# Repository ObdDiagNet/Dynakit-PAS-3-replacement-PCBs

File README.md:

Dynakit PAS-3 replacement PCBs
==========================================
A set of circuit boards for PAS-3 preamplifier including PC-5 line Stage and PC-6 Phono Stage plus Capacitor Board.

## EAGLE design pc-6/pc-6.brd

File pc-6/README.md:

Dynakit PAS-3 PC-6 Phono Stage circuit board
==========================================
The boards retain the original Dynakit PAS circuitry but uses available PCB through hole capacitors.
The boards retain the original Dynakit PAS circuitry but uses available through hole capacitors. Original solder pad numbering is retained and silk-screened on circuit board.

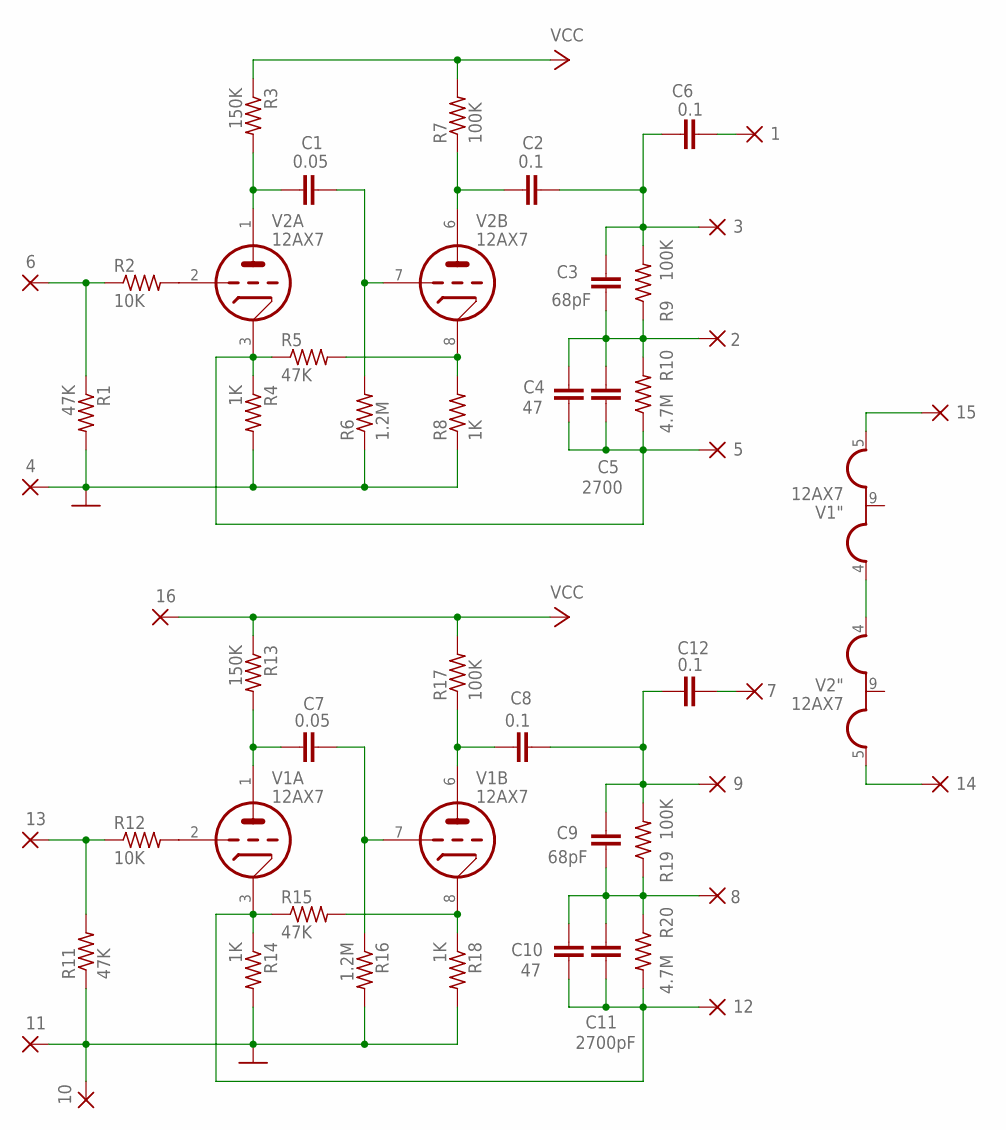
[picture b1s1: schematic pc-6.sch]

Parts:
1, 2, 3, 4, 5, 6, 7, 8, 9, 10, 11, 12, 13, 14, 15, 16: WIREPAD3,17/1,3M; 3,17/1,13M
C1, C7: 0.05; C10B4
C2, C6, C8, C12: 0.1; C10B4
C3, C9: 68pF; C5B2.5
C4, C10: 47; C5B2.5
C5: 2700; C5B2.5
C11: 2700pF; C5B2.5
R1, R5, R11, R15: 47K; 0411/15
R2, R12: 10K; 0411/15
R3, R13: 150K; 0411/15
R4, R8, R14, R18: 1K; 0411/15
R6, R16: 1.2M; 0411/15
R7, R9, R17, R19: 100K; 0411/15
R10, R20: 4.7M; 0411/15
V1, V2: 12AX7; NOVAL

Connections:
GND: 4.1, 10.1, 11.1, R1.2, R4.2, R6.1, R8.1, R11.1, R14.2, R16.2, R18.2
unnamed: C7.2, R13.2, V1.1 (TA)
unnamed: R12.2, V1.2 (TG)
unnamed: 8.1, C9.1, C10.1, C11.1, R19.1, R20.1
unnamed: 7.1, C12.2
unnamed: C7.1, R16.1, V1.7 (TG)
unnamed: C1.1, R6.2, V2.7 (TG)
unnamed: 3.1, C2.1, C3.2, C6.1, R9.2
unnamed: 13.1, R11.2, R12.1
unnamed: R15.2, R18.1, V1.8 (TK)
unnamed: C8.1, R17.1, V1.6 (TA)
unnamed: 9.1, C8.2, C9.2, C12.1, R19.2
unnamed: C1.2, R3.2, V2.1 (TA)
unnamed: R2.2, V2.2 (TG)
unnamed: 12.1, C10.2, C11.2, R14.1, R15.1, R20.2, V1.3 (TK)
unnamed: 2.1, C3.1, C4.1, C5.1, R9.1, R10.2
unnamed: 1.1, C6.2
unnamed: R5.2, R8.2, V2.8 (TK)
unnamed: C2.2, R7.1, V2.6 (TA)
unnamed: 5.1, C4.2, C5.2, R4.1, R5.1, R10.1, V2.3 (TK)
unnamed: 6.1, R1.1, R2.1
unnamed: 15.1, V1.5 (H3)
unnamed: 14.1, V2.5 (H3)
unnamed: V1.4 (H1), V2.4 (H1)
VCC: 16.1, R3.1, R7.2, R13.1, R17.2

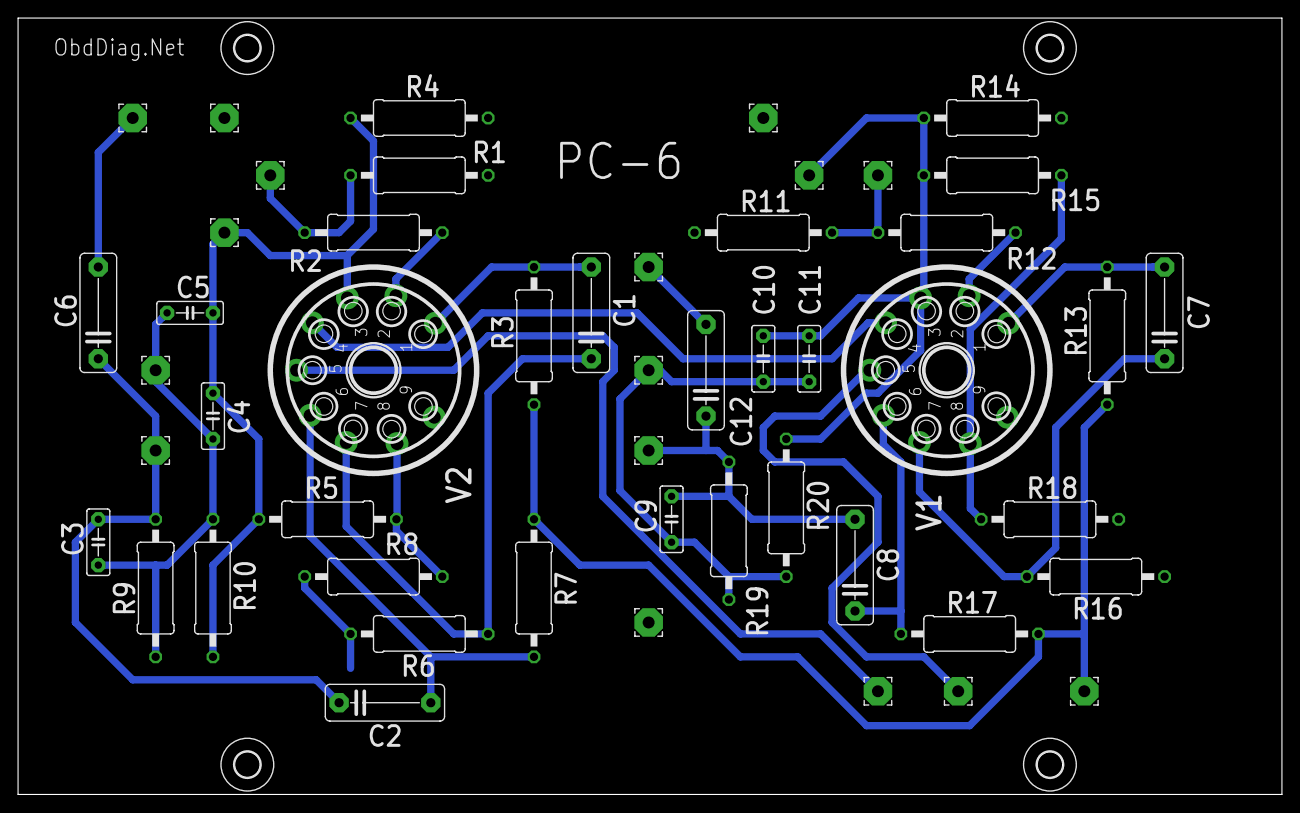
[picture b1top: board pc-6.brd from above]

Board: 2 copper layers, 140.0 x 86.0 mm, 54 parts (0 on the bottom side), 25 nets.

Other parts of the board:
U$1, U$2, U$3, U$4: 2,8

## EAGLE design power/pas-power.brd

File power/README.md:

Dynaco PAS-3 Capacitor Board
==========================================

This board replaces the large can capacitor in the power supply section of the Dynaco PAS-3 preamplifier, as well as the selenium filament rectifier and 
the two large filament filter caps. Exact replacements for the original can capacitors are difficult to find. The board uses readily available PCB through hole capacitors.

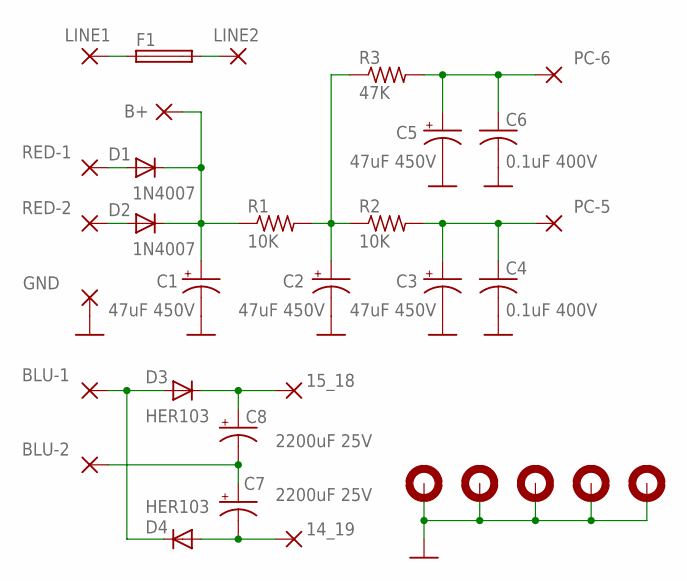
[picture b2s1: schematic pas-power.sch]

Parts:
14_19, 15_18: 3,81/1,4
B+: 3,81/1,4
BLU-1, BLU-2: 3,81/1,4
C1, C2, C3, C5: 47uF 450V; E7,5-16
C4, C6: 0.1uF 400V; C102-043X133
C7, C8: 2200uF 25V; E5-10,5
D1, D2: 1N4007; DO41-10
D3, D4: HER103; DO41-10
F1: FUSESHK20L; SHK20L
GND: 3,81/1,4
H1: MOUNT-PAD-ROUND4.3; 4,3-PAD
H2, H3, H4, H5: MOUNT-PAD-ROUND3.3; 3,3-PAD
LINE1, LINE2: 3,81/1,4
PC-5, PC-6: 3,81/1,4
R1, R2: 10K; 0309/12
R3: 47K; 0309/12
RED-1, RED-2: 3,81/1,4

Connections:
GND: C1.-, C2.-, C3.-, C4.2, C5.-, C6.2, GND.1, H1.B4,3, H2.B3,3, H3.B3,3, H4.B3,3, H5.B3,3
unnamed: D1.A, RED-1.1
unnamed: D2.A, RED-2.1
unnamed: B+.1, C1.+, D1.C, D2.C, R1.1
unnamed: C2.+, R1.2, R2.1, R3.1
unnamed: C3.+, C4.1, PC-5.1, R2.2
unnamed: BLU-1.1, D3.A, D4.C
unnamed: C5.+, C6.1, PC-6.1, R3.2
unnamed: 14_19.1, C7.-, D4.A
unnamed: 15_18.1, C8.+, D3.C
unnamed: BLU-2.1, C7.+, C8.-
unnamed: F1.2A (2), LINE2.1
unnamed: F1.1A (1), LINE1.1

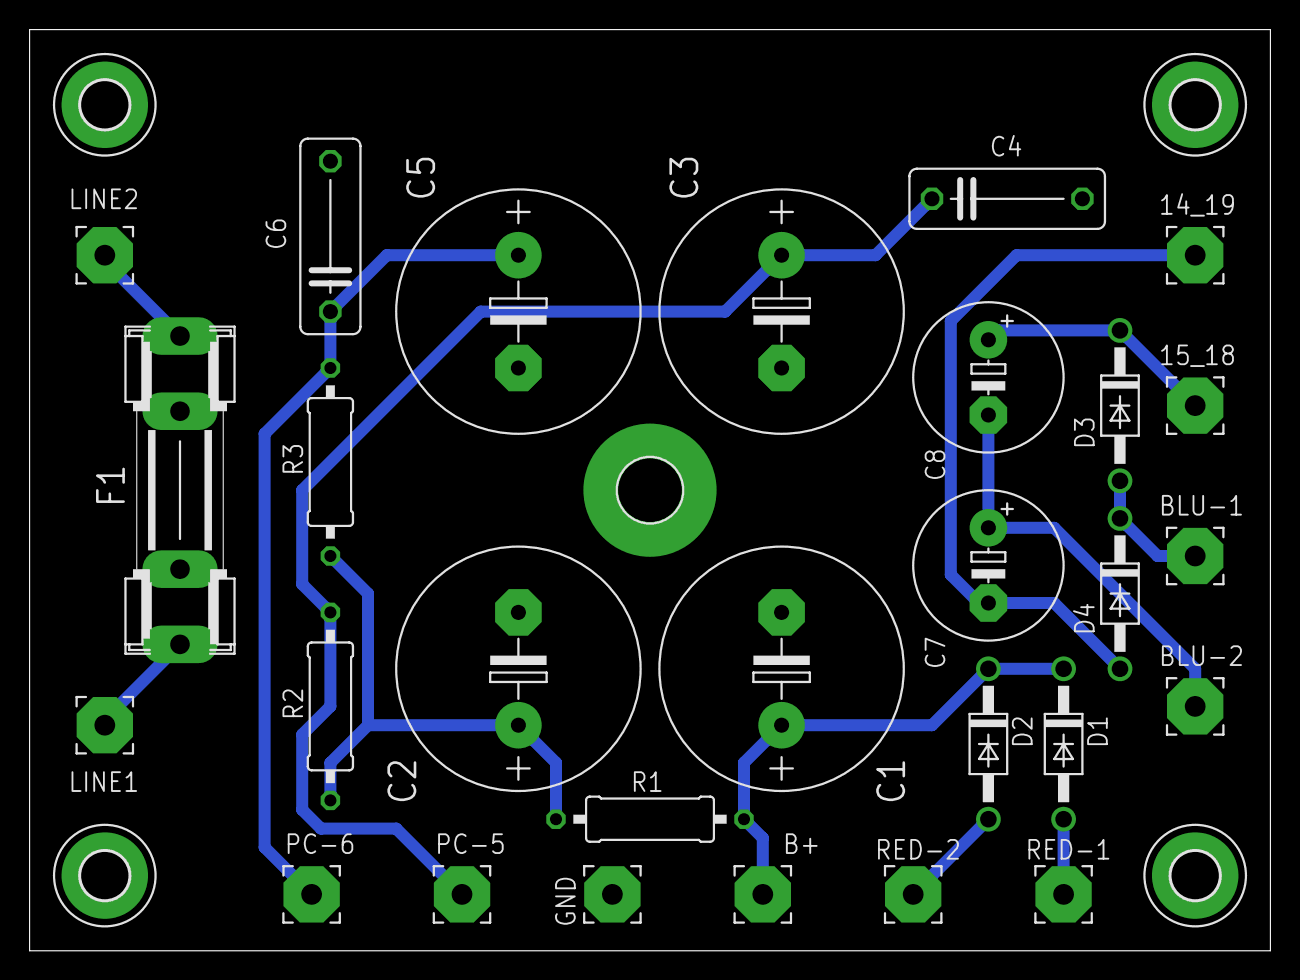
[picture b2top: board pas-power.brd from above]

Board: 2 copper layers, 83.8 x 62.2 mm, 33 parts (0 on the bottom side), 13 nets.

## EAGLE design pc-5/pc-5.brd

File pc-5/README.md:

Dynakit PAS-3 PC-5 Line Stage circuit board
==========================================
The boards retain the original Dynakit PAS circuitry but uses available through hole capacitors. Original solder pad numbering is retained and silk-screened on circuit board.

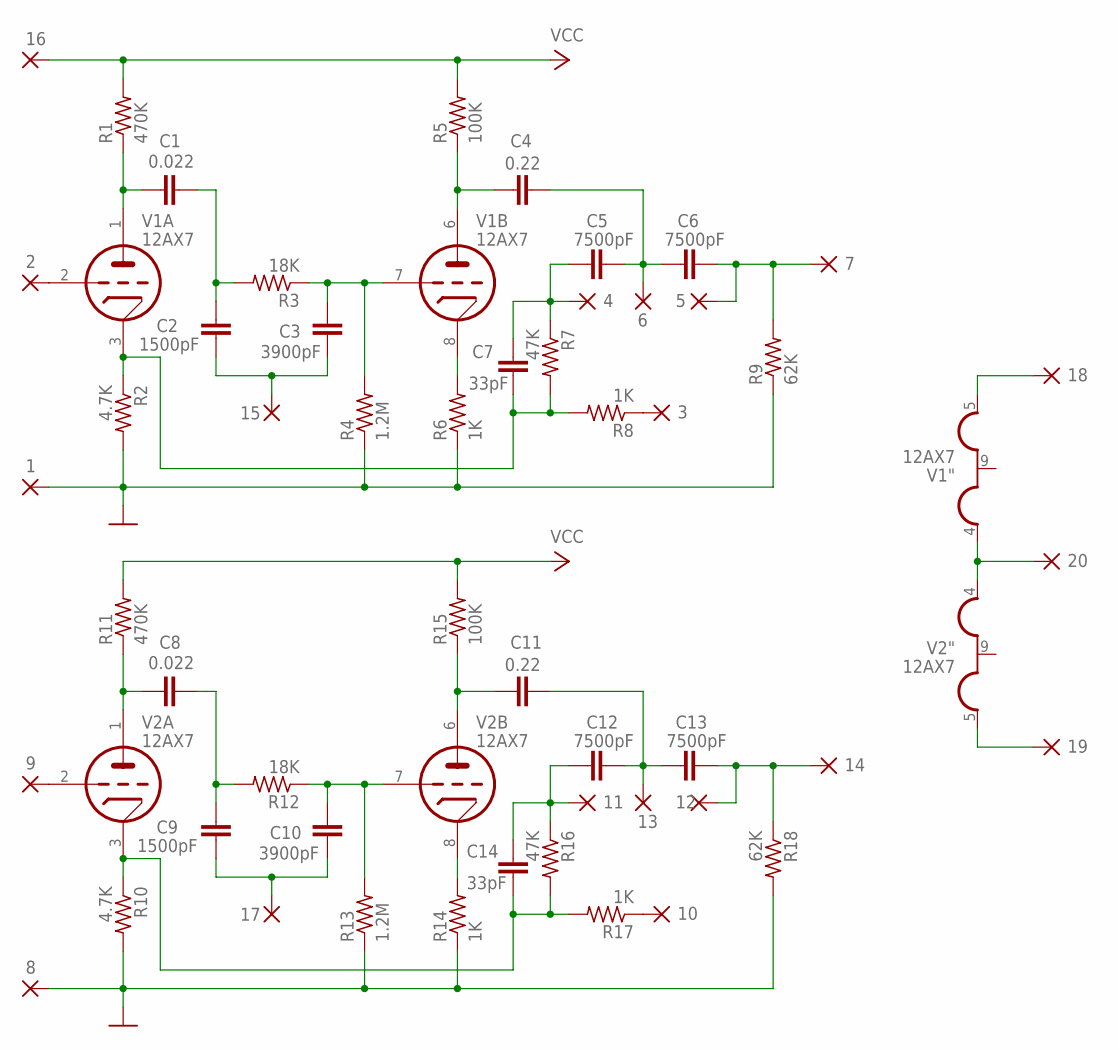
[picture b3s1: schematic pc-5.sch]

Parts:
1, 2, 3, 4, 5, 6, 7, 8, 9, 10, 11, 12, 13, 14, 15, 16, 17, 18, 19, 20: WIREPAD3,17/1,3M; 3,17/1,13M
C1, C8: 0.022; C7.5B3
C2, C9: 1500pF; C5B2.5
C3, C10: 3900pF; C5B2.5
C4, C11: 0.22; C10B4
C5, C6, C12, C13: 7500pF; C10B4
C7, C14: 33pF; C5B2.5
R1, R11: 470K; 0411/15
R2, R10: 4.7K; 0411/15
R3, R12: 18K; 0411/15
R4, R13: 1.2M; 0411/15
R5, R15: 100K; 0411/15
R6, R8, R14, R17: 1K; 0411/15
R7, R16: 47K; 0411/15
R9, R18: 62K; 0411/15
V1, V2: 12AX7; NOVAL

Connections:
GND: 1.1, 8.1, R2.2, R4.1, R6.1, R9.1, R10.2, R13.1, R14.1, R18.2
unnamed: C1.1, R1.1, V1.1 (TA)
unnamed: C1.2, C2.1, R3.2
unnamed: C3.1, R3.1, R4.2, V1.7 (TG)
unnamed: 15.1, C2.2, C3.2
unnamed: 2.1, V1.2 (TG)
unnamed: R6.2, V1.8 (TK)
unnamed: 3.1, R8.1
unnamed: C4.1, R5.1, V1.6 (TA)
unnamed: 6.1, C4.2, C5.2, C6.1
unnamed: C8.1, R11.1, V2.1 (TA)
unnamed: 4.1, C5.1, C7.1, R7.1
unnamed: C7.2, R2.1, R7.2, R8.2, V1.3 (TK)
unnamed: 5.1, 7.1, C6.2, R9.2
unnamed: C8.2, C9.1, R12.2
unnamed: C10.1, R12.1, R13.2, V2.7 (TG)
unnamed: 17.1, C9.2, C10.2
unnamed: R14.2, V2.8 (TK)
unnamed: C11.1, R15.1, V2.6 (TA)
unnamed: 13.1, C11.2, C12.2, C13.1
unnamed: 11.1, C12.1, C14.1, R16.1
unnamed: C14.2, R10.1, R16.2, R17.2, V2.3 (TK)
unnamed: 12.1, 14.1, C13.2, R18.1
unnamed: 10.1, R17.1
unnamed: 9.1, V2.2 (TG)
unnamed: 18.1, V1.5 (H3)
unnamed: 19.1, V2.5 (H3)
unnamed: 20.1, V1.4 (H1), V2.4 (H1)
VCC: 16.1, R1.2, R5.2, R11.2, R15.2

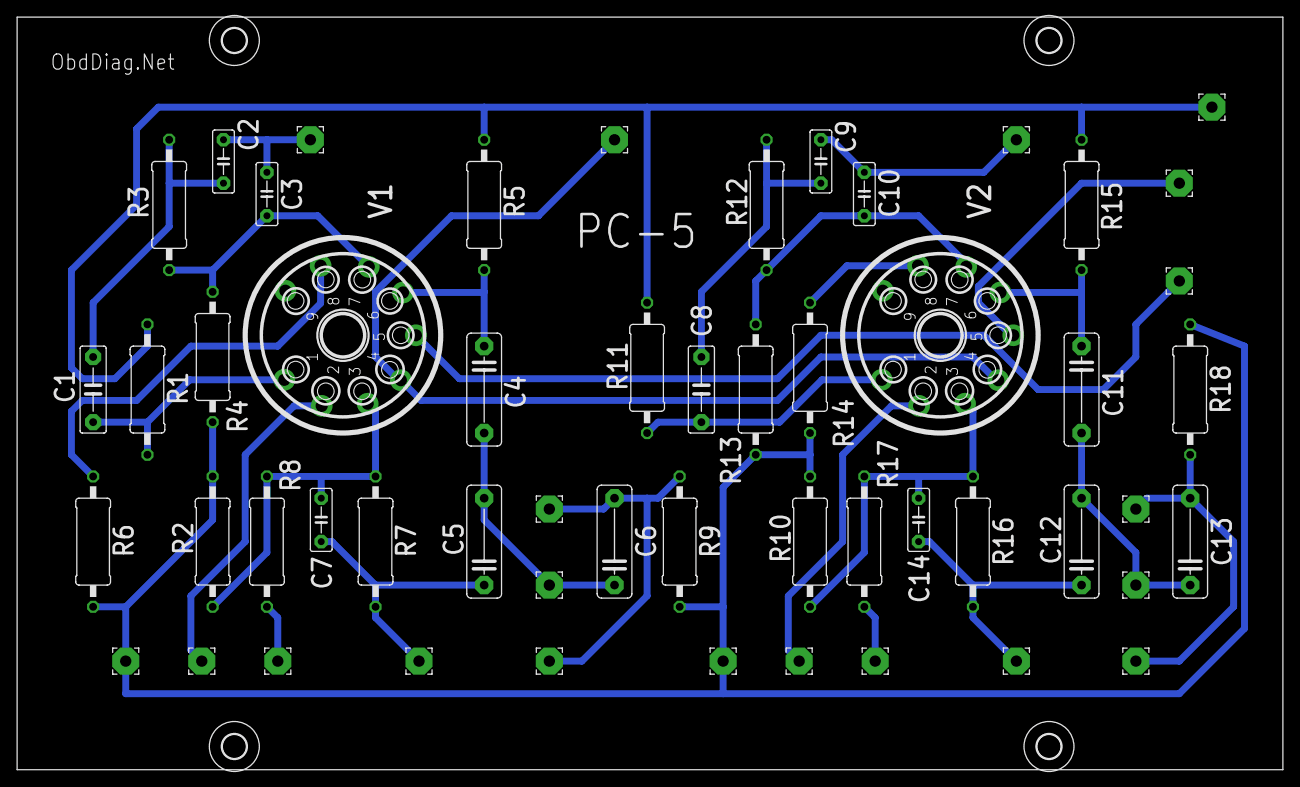
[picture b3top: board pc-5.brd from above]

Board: 2 copper layers, 148.0 x 88.0 mm, 58 parts (0 on the bottom side), 29 nets.

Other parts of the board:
U$1, U$2, U$3, U$4: 2,8

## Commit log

2024-09-23 Initial release
2024-09-23 Next pix
2024-09-23 Background
2024-09-23 Dynaco PAS-3 capacitor Board description
2024-09-23 Moved
2024-09-23 Schematic in pdf
2024-09-23 More readme
2024-09-23 More pdfs
2024-09-23 More descriptions
2024-09-25 Image
2024-09-25 More images
2024-09-25 Fixed a wrong size for R3/R13
